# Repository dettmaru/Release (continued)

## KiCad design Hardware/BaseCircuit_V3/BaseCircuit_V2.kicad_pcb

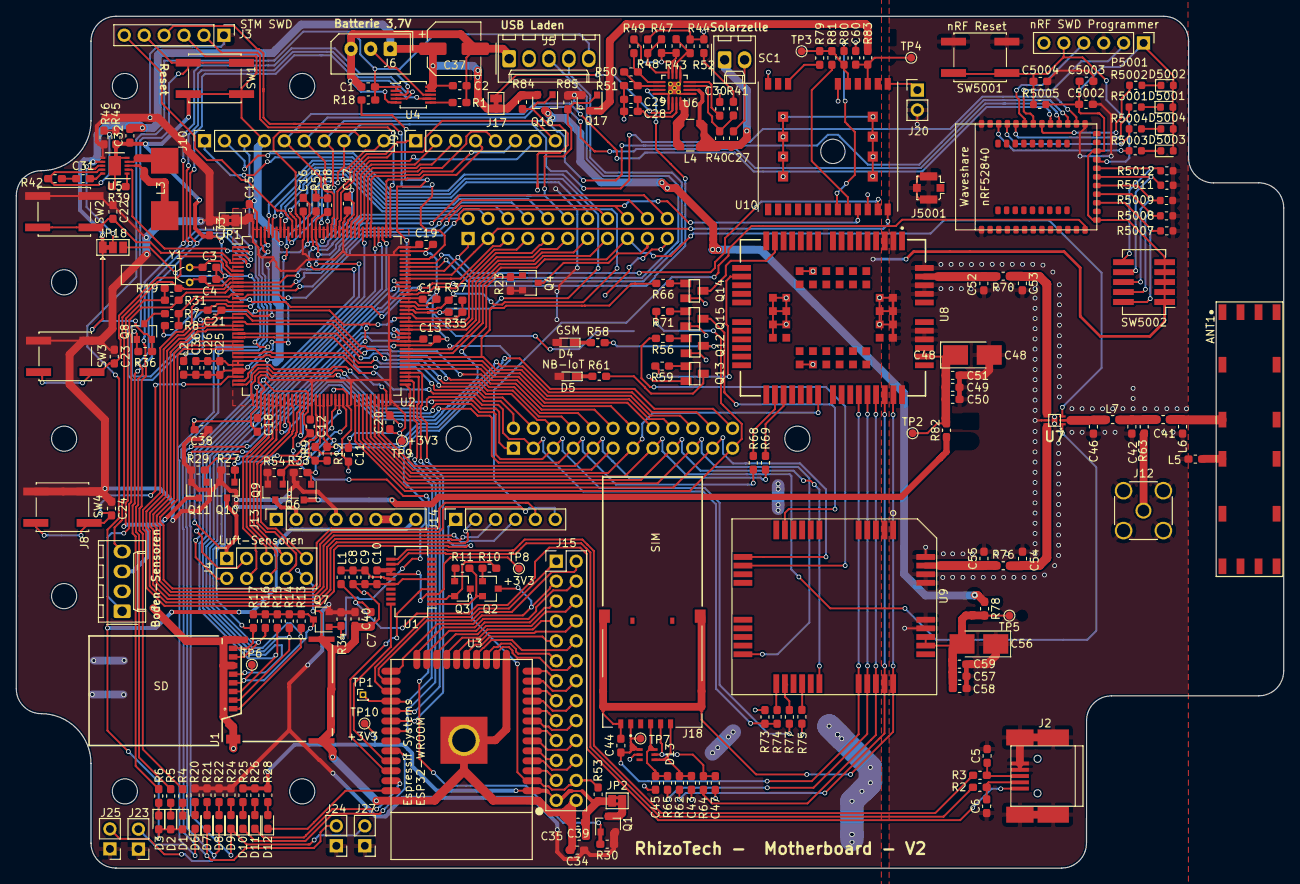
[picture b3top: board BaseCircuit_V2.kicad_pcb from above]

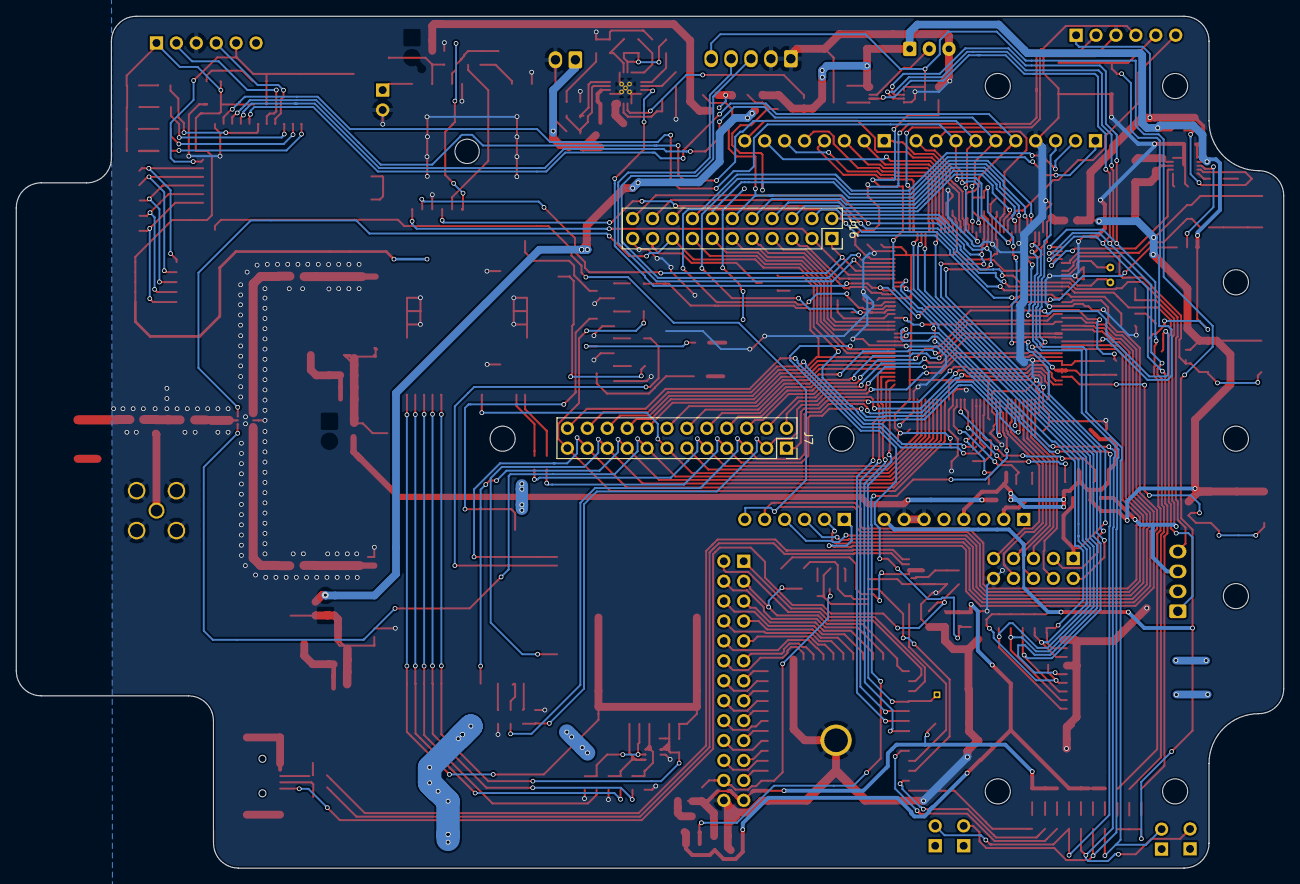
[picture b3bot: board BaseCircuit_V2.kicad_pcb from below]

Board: 2 copper layers, 161.6 x 108.6 mm, 259 parts (2 on the bottom side), 259 nets.

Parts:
ANT1: Lucida; Antenova_Lucida
C1, C2, C25: 1µ; C_0603_1608Metric_Pad1.05x0.95mm_HandSolder
C3, C4: 4p7; C_0603_1608Metric_Pad1.05x0.95mm_HandSolder
C5, C6: 47p; C_0603_1608Metric_Pad1.05x0.95mm_HandSolder
C7, C28, C30, C36: 10n; C_0603_1608Metric_Pad1.05x0.95mm_HandSolder
C8, C10, C11, C12, C13, C14, C15, C16, C17, C18, C19, C20, C21, C22, C23, C24, C26, C31, C35, C44, C49, C57, C60: 100n; C_0603_1608Metric_Pad1.05x0.95mm_HandSolder
C9, C27, C29: 4µ7; C_0603_1608Metric_Pad1.05x0.95mm_HandSolder
C32: 10µ; C_0603_1608Metric_Pad1.05x0.95mm_HandSolder
C33, C34, C38, C39, C40: 22µ; C_0603_1608Metric_Pad1.05x0.95mm_HandSolder
C37: 470µ; CP_Elec_6.3x7.7
C41: 2p2; C_0603_1608Metric_Pad1.05x0.95mm_HandSolder
C42: Not fitted; C_0603_1608Metric_Pad1.05x0.95mm_HandSolder
C43, C45, C47, C59: 33p; C_0603_1608Metric_Pad1.05x0.95mm_HandSolder
C46: 0p5; C_0603_1608Metric_Pad1.05x0.95mm_HandSolder
C48, C56: 100µ; Tantal_Cap_100u
C50: 100p; C_0603_1608Metric_Pad1.05x0.95mm_HandSolder
C51: 22p; C_0603_1608Metric_Pad1.05x0.95mm_HandSolder
C52, C53, C54, C55: NM; C_0603_1608Metric_Pad1.05x0.95mm_HandSolder
C58: 10p; C_0603_1608Metric_Pad1.05x0.95mm_HandSolder
C5002: 4.7µF; C_0603_1608Metric_Pad1.05x0.95mm_HandSolder
C5003, C5004: 100nF; C_0603_1608Metric_Pad1.05x0.95mm_HandSolder
D1, D2, D8, D10: Rot; LED_0603_1608Metric_Pad1.05x0.95mm_HandSolder
D3, D9, D11: Grün; LED_0603_1608Metric_Pad1.05x0.95mm_HandSolder
D4: GSM_NET; GSM_LED
D5: NB-IoT_NET; NB-IoT_LED
D6, D7, D12: Gelb; LED_0603_1608Metric_Pad1.05x0.95mm_HandSolder
D13: SMF05C.TCT; SC70-6
D5001, D5002, D5003, D5004: LED; LED_0603_1608Metric
H6, H7, H8, H9, H10, H11, H12, H13, H14: MountingHole; MountingHole_3.2mm_M3
J1: Micro_SD_Card; 503398-1892
J2: USB B mini; USB_Mini-B
J3: CONN_01X06; PinHeader_1x06_P2.54mm_Vertical
J4: Conn_2x5_Temp; PinHeader_2x05_P2.54mm_Vertical
J5: Conn_01x05; Molex_KK-254_AE-6410-05A_1x05_P2.54mm_Vertical
J6: CONN_01X03; Molex_SPOX_5267-03A_1x03_P2.50mm_Vertical
J7: Conn_02x12_Odd_Even; PinSocket_2x12_P2.54mm_Vertical
J8: Conn_1x4_Soil; Molex_KK-254_AE-6410-04A_1x04_P2.54mm_Vertical
J9, J13: Conn_01x08; PinSocket_1x08_P2.54mm_Vertical
J10: Conn_01x10; PinSocket_1x10_P2.54mm_Vertical
J12: Conn_Coaxial; SMA_Amphenol_132134_Vertical
J14: Conn_01x06; PinSocket_1x06_P2.54mm_Vertical
J15: Conn_02x13_ESP; PinHeader_2x13_P2.54mm_Vertical
J16: Conn_02x11_Odd_Even; PinSocket_2x11_P2.54mm_Vertical
J17: GS2; SolderJumper-2_P1.3mm_Bridged_Pad1.0x1.5mm
J18: Micro-SIM; CONN_78646-3001
J20, J23, J24, J25, J27: Conn_01x02_Male; PinHeader_1x02_P2.54mm_Vertical
J5001: SMA Connector; U.FL_Molex_MCRF_73412-0110_Vertical
JP1: STM Bridge; SolderJumper-2_P1.3mm_Bridged2Bar_Pad1.0x1.5mm
JP2: ESP Bridge; SolderJumper-2_P1.3mm_Bridged2Bar_Pad1.0x1.5mm
JP18: SolderJumper_3_Bridged12; SolderJumper-3_P1.3mm_Bridged12_Pad1.0x1.5mm
L1, L2: Ferrite_Bead; L_0603_1608Metric_Pad1.05x0.95mm_HandSolder
L3: 10µ; MGV0603100M
L4: 22µ; L_Coilcraft_LPS4018
L5, L6: 15n; L_0603_1608Metric_Pad1.05x0.95mm_HandSolder
L7: 3n3; L_0603_1608Metric_Pad1.05x0.95mm_HandSolder
P5001: SWD Programmer; PinHeader_1x06_P2.54mm_Vertical
Q1, Q4, Q6, Q7, Q8, Q9, Q10, Q11, Q16, Q17: DMP2170; SOT-23
Q2, Q3: MMBT2222; SOT-23
Q12, Q13, Q14, Q15: MMBT2222A; SOT23
R1, R4, R5, R6, R7, R8, R18, R19, R20, R21, R22, R24, R25, R26, R28, R31, R58, R61, R68, R69, R74, R77: 1k; R_0603_1608Metric_Pad1.05x0.95mm_HandSolder
R2, R3: 27R; R_0603_1608Metric_Pad1.05x0.95mm_HandSolder
R9, R12, R35, R37, R38, R55, R56, R59, R66, R71: 4k7; R_0603_1608Metric_Pad1.05x0.95mm_HandSolder
R10, R11, R53, R79: 10k; R_0603_1608Metric_Pad1.05x0.95mm_HandSolder
R13, R14, R15, R16, R17: 47k; R_0603_1608Metric_Pad1.05x0.95mm_HandSolder
R23, R27, R29, R30, R33, R34, R36, R54, R84, R85: 1M; R_0603_1608Metric_Pad1.05x0.95mm_HandSolder
R39: 60k4; R_0603_1608Metric_Pad1.05x0.95mm_HandSolder
R40: 3M32; R_0603_1608Metric_Pad1.05x0.95mm_HandSolder
R41: 10M; R_0603_1608Metric_Pad1.05x0.95mm_HandSolder
R42: 15k; R_0603_1608Metric_Pad1.05x0.95mm_HandSolder
R43: 5M49; R_0603_1608Metric_Pad1.05x0.95mm_HandSolder
R44: 4M42; R_0603_1608Metric_Pad1.05x0.95mm_HandSolder
R45: 200k; R_0603_1608Metric_Pad1.05x0.95mm_HandSolder
R46: 340k; R_0603_1608Metric_Pad1.05x0.95mm_HandSolder
R47, R48: 4M99; R_0603_1608Metric_Pad1.05x0.95mm_HandSolder
R49: 1M73; R_0603_1608Metric_Pad1.05x0.95mm_HandSolder
R50: 3M92; R_0603_1608Metric_Pad1.05x0.95mm_HandSolder
R51: 4M32; R_0603_1608Metric_Pad1.05x0.95mm_HandSolder
R52: 6M65; R_0603_1608Metric_Pad1.05x0.95mm_HandSolder
R62, R64, R65: 22R; R_0603_1608Metric_Pad1.05x0.95mm_HandSolder
R63, R70, R75, R76, R78, R82, R83: 0R; R_0603_1608Metric_Pad1.05x0.95mm_HandSolder
R73: 5k6; R_0603_1608Metric_Pad1.05x0.95mm_HandSolder
R80, R81: 2k2; R_0603_1608Metric_Pad1.05x0.95mm_HandSolder
R5001, R5002, R5003, R5004: 220; R_0603_1608Metric
R5005, R5007, R5008, R5009, R5011, R5012: 10k; R_0603_1608Metric
SC1: Solar_Cell; Molex_KK-254_AE-6410-02A_1x02_P2.54mm_Vertical
SW1, SW2, SW3, SW4, SW5001: SW_Push; SW_SPST_EVQQ2
SW5002: SW_DIP_x05; SW_DIP_SPSTx05_Slide_KingTek_DSHP05TJ_W5.25mm_P1.27mm_JPin
TP1: SE_REA; PinHeader_1x01_P1.00mm_Vertical
TP2, TP4, TP8, TP9, TP10: +3V3; TestPoint_Pad_D1.0mm
TP3: +1V8; TestPoint_Pad_D1.0mm
TP5: +VBATT; TestPoint_Pad_D1.0mm
TP6: U_SD; TestPoint_Pad_D1.0mm
TP7: U_SIM; TestPoint_Pad_D1.0mm
U1: FT231XS; SSOP-20_3.9x8.7mm_P0.635mm
U2: STM32L496Zx; TQFP-144_20x20mm_P0.5mm
U3: ESP32-WROOM
U4: MCP73833; MSOP-10_3x3mm_P0.5mm
U5: LTC3440; DFN-10-1EP_3x3mm_P0.5mm_EP1.55x2.48mm
U6: BQ25504; QFN-16-1EP_3x3mm_Pitch0.5mm_ThermalVias_HandSoldering
U7: SKY13370-374LF; SKY13370_374LF
U8: BC95G; BC95-B8
U9: M95; XCVR_M95
U10: A2235-H; XCVR_A2235-H
U5001: nRF52840; Waveshare_nRF528840
Y1: 32.768kHz; Crystal_C26-LF_D2.1mm_L6.5mm_Horizontal

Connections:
1V8: R79.2, R80.2, R81.2, TP3.1, U10.5
+3.3VP: C10.1, TP8.1, U1.3, U1.13, U1.14
+5VL: C1.2, D1.2, D2.2, D3.2, J5.5, J13.8, R18.1, U4.1, U4.2
+5VP: C8.1, C9.1, L1.2, U1.15
+BATT: C2.1, C32.2, C37.1, J6.1, J17.1, JP18.1, Q8.2, Q16.2, R36.1, R84.1, U4.9, U4.10, U5.7
/BT1: C22.2, SW2.2, U2.5
/BT2: C23.2, SW3.2, U2.7
/BT3: C24.2, SW4.2, U2.34
/CLK: J15.8, U3.20
/CMD: J15.9, U3.19
/D_LOAD+: J5.3, U2.104
/D_LOAD-: J5.4, U2.103
/ESP_GPIO0: J15.3, Q2.3, U3.25
/ESP_ON: Q1.1, R30.2, U2.49
/ESP_RESET: J15.24, Q3.3, R53.1, U3.3
/ESP_RXD0: U1.20, U3.34
/ESP_TXD0: U1.4, U3.35
/IO2: J15.4, U3.24
/IO4: J15.2, U3.26
/IO5: U2.75, U3.29
/IO12: J15.13, U3.14
/IO13: J15.12, U3.16
/IO14: J15.14, U3.13
/IO15: J15.5, U3.23
/IO16: J15.1, U3.27
/IO17: TP1.1, U2.73, U3.28
/IO18: U2.76, U3.30
/IO19: U2.74, U3.31
/IO21: D10.1, U3.33
/IO22: D11.1, U3.36
/IO23: D12.1, U3.37
/IO25: J15.17, U3.10
/IO26: J15.16, U3.11
/IO27: J15.15, U3.12
/IO32: J15.19, U3.8
/IO33: J15.18, U3.9
/IO34: J15.21, U3.6
/IO35: J15.20, U3.7
/Interfaces/+5V_ESP: C7.1, J2.1, L1.1
/Interfaces/D+_ESP: C5.1, J2.3, R3.2
/Interfaces/D-_ESP: C6.1, J2.2, R2.2
/Interfaces/DTR: Q2.2, R11.2, U1.1
/Interfaces/RTS: Q3.2, R10.2, U1.2
/LED1: D6.1, J23.2, U2.141
/LED2: D7.1, J24.2, U2.142
/LED3: D8.1, J25.2, U2.85
/LED4: D9.1, J27.2, U2.86
/LOAD_PG: R6.2, U2.3, U4.7
/LOAD_STAT1: R4.2, U2.1, U4.3
/LOAD_STAT2: R5.2, U2.2, U4.4
/MODE_SYNC: U2.4, U5.2
/NRST: J3.5, SW1.1, U2.25
/PA1: J7.1, U2.35
/PA4: J4.4, U2.40
/PA5: J4.5, U2.41
/PA6: J4.6, U2.42
/PA7: J4.7, U2.43
/PA8: J16.5, U2.100
/PA15: J9.4, U2.110
/PB0: J4.8, U2.46
/PB1: J4.9, U2.47
/PB3: J16.6, U2.133
/PB5: J10.10, U2.135
/PB6: J16.8, U2.136
/PB7: J16.10, U2.137
/PB8: J16.12, Q17.1, R85.2, U2.139
/PB9: J16.14, Q16.1, R84.2, U2.140
/PB10: J7.11, U2.69
/PC1: J14.5, U2.27
/PC2: J7.4, U2.28
/PC3: J7.2, U2.29
/PC5: R18.2, U2.45
/PC6: J16.7, U2.96
/PC7: JP18.3, U2.97, U6.11
/PC8: J1.7, R16.2, U2.98
/PC9: J1.8, R17.2, U2.99
/PC10: J1.1, R13.2, U2.111
/PC11: J1.2, R14.2, U2.112
/PC12: J1.5, U2.113
/PD0: J9.6, U2.114
/PD1: J9.5, U2.115
/PD2: J1.3, R15.2, U2.116
/PD3: J9.3, U2.117
/PD4: J9.2, U2.118
/PD5: J9.7, U2.119
/PD6: J9.8, U2.122
/PD7: J9.1, U2.123
/PD8: J7.14, U2.77
/PD9: J7.16, U2.78
/PD10: J7.18, U2.79
/PD13: J16.15, Q7.1, R34.2, U2.82
/PE7: Q10.1, R27.2, U2.58
/PE8: Q11.1, R29.2, U2.59
/PE9: Q9.1, R54.2, U2.60
/PF0: J8.4, J16.22, R19.2, U2.10
/PF1: J8.1, J16.20, R31.2, U2.11
/PF3: R7.2, R8.1, U2.13
/PF4: J16.16, U2.14
/PF5: J14.1, U2.15
/PF6: J7.8, U2.18
/PF7: J14.2, U2.19
/PF8: J7.12, U2.20
/PF9: J14.3, U2.21
/PF10: J14.4, U2.22
/PF12: Q4.1, R23.2, U2.50
/PF13: R9.2, R12.2, U2.53
/PF14: J7.24, R9.1, U2.54
/PF15: J7.22, R12.1, U2.55
/PG0: Q6.1, R33.2, U2.56
/PG2: J16.13, U2.87
/PG3: J16.11, U2.88
/PG4: J16.9, U2.89
/PG5: Q8.1, R36.2, U2.90
/PG6: R35.1, R37.1, U2.91
/PG7: J10.1, R35.2, U2.92
/PG8: J10.2, R37.2, U2.93
/PG13: J4.2, J16.2, R38.2, U2.128
/PG14: J4.3, J16.4, R55.2, U2.129
/PG15: J10.9, U2.132
/PH0: J7.10, U2.23
/PH1: J7.6, U2.24
/Powersupply/THERM: J6.2, U4.8
/SD1: J15.6, U3.22
/SD2: J15.11, U3.17
/SD3: J15.10, U3.18
/SDO: J15.7, U3.21
/SENSOR_VN: J15.22, U3.5
/SENSOR_VP: J15.23, U3.4
/SWCLK: J3.2, U2.109
/SWDIO: J3.4, U2.105
/TRACESWO: J3.6, U2.134
/VREF: C25.2, C26.2, C36.2, J10.3, L2.2, U2.32, U2.33
ANT: C46.1, L7.2, U7.2
ANT_BC95: J16.17, U2.81, U7.3
ANT_M95: J7.15, U2.67, U7.1
BC95_NETLIGHT: R59.2, U8.18
BC95_RST: J7.20, R66.2, U2.80
ESP3V3: C35.1, C39.1, J15.25, JP2.2, R25.1, R26.1, R28.1, R53.2, TP10.1, U3.2
GND: C1.1, C2.2, C3.2, C4.2, C5.2, C6.2, C7.2, C8.2, C9.2, C10.2, C11.2, C12.2, C13.2, C14.2, C15.2, C16.2, C17.2, C18.2, C19.2, C20.2, C21.2, C25.1, C26.1, C27.1, C28.2, C29.2, C30.2, C32.1, C33.2, C34.2, C35.2, C36.1, C37.2, C38.2, C39.2, C40.2, C42.2, C43.2, C45.2, C46.2, C47.2, C48.2, C49.2, C50.2, C51.2, C52.2, C53.2, C54.2, C55.2, C56.1, C57.1, C58.1, C59.1, C60.1, C5002.2, C5003.2, C5004.2, D13.2, J1.6, J1.9, J2.4, J2.5, J2.6, J3.3, J4.10, J5.1, J5.2, J6.3, J8.2, J10.4, J12.2, J13.6, J13.7, J15.26, J16.21, J20.2, J5001.2, L5.1, L6.2, P5001.3, Q12.2, Q13.2, Q14.2, Q15.2, R1.2, R8.2, R39.2, R44.2, R45.1, R48.2, R51.2, R52.1, R73.2, R75.2, R5007.2, R5008.2, R5009.2, R5011.2, R5012.2, SC1.2, SW1.2, SW5001.2, U1.6, U1.16, U2.16, U2.30, U2.31, U2.38, U2.51, U2.61, U2.71, U2.83, U2.94, U2.107, U2.120, U2.130, U2.138, U2.143, U3.1, U3.15, U3.38, U3.39, U4.5, U5.5, U6.1, U6.5, U6.12, U6.13, U6.17, U7.5, U7.7, U8.2, U8.43, U8.47, U8.48, U8.51, U8.52, U8.54, U8.59, U8.60, U8.61, U8.62, U8.63, U8.64, U8.65, U8.66, U8.71, U8.72, U8.73, U8.74, U8.81, U8.82, U8.83, U8.92, U8.93, U8.94, U9.35, U9.36, U9.37, U9.38, U9.40, U10.6, U10.9, U10.20, U10.23, U10.24, U10.25, U10.26, U10.27, U10.28, U10.29, U10.30, U5001.B7
GPS_ON_SW: J16.18, U2.12, U10.19
LED0: R5001.2, U5001.U24
LED1: R5002.2, U5001.W24
LED2: R5003.2, U5001.L24
LED3: R5004.2, U5001.R24
M95_DTR: J7.19, U2.65, U9.20
M95_NETLIGHT: R56.2, U9.13
M95_ON_SW: J7.23, R71.2, U2.63
M95_STATUS: J7.21, U2.64, U9.12
unnamed: ANT1.3, C41.2, L6.1
unnamed: ANT1.4, L5.2
unnamed: C3.1, U2.8, Y1.1
unnamed: C4.1, U2.9, Y1.2
unnamed: C27.2, L4.1, R40.1, SC1.1, U6.2
unnamed: C28.1, C29.1, U6.15
unnamed: C30.1, U6.4
unnamed: C31.1, U5.10
unnamed: C31.2, R42.1
unnamed: C41.1, C42.1, L7.1, R63.2
unnamed: C43.1, D13.4, J18.C3, R62.1
unnamed: C45.1, D13.6, J18.C2, R65.1
unnamed: C47.1, D13.5, J18.C7, R64.1
unnamed: C48.1, C49.1, C50.1, C51.1, R82.1, TP2.1, U8.45, U8.46
unnamed: C52.1, R70.2, U8.53
unnamed: C55.1, R76.1, U9.39
unnamed: C56.2, C57.2, C58.2, C59.2, R78.2, TP5.1, U9.33, U9.34
unnamed: C60.2, R83.2, TP4.1, U10.3
unnamed: D1.1, R4.1
unnamed: D2.1, R5.1
unnamed: D3.1, R6.1
unnamed: D4.1, R58.2
unnamed: D5.1, R61.2
unnamed: D6.2, R20.2
unnamed: D7.2, R21.2
unnamed: D8.2, R22.2
unnamed: D9.2, R24.2
unnamed: D10.2, R25.2
unnamed: D11.2, R26.2
unnamed: D12.2, R28.2
unnamed: D5001.1, R5001.1
unnamed: D5002.1, R5002.1
unnamed: D5003.1, R5003.1
unnamed: D5004.1, R5004.1
unnamed: J1.4, Q7.3, R13.1, R14.1, R15.1, R16.1, R17.1, TP6.1
unnamed: J12.1, R63.1
unnamed: J17.2, U6.14
unnamed: J20.1, U10.1
unnamed: JP2.1, Q1.3
unnamed: JP18.2, U5.8
unnamed: L3.1, U5.4
unnamed: L3.2, U5.3
unnamed: L4.2, U6.16
unnamed: Q2.1, R10.1
unnamed: Q3.1, R11.1
unnamed: Q8.3, R7.1
unnamed: Q12.1, R56.1
unnamed: Q12.3, R58.1
unnamed: Q13.1, R59.1
unnamed: Q13.3, R61.1
unnamed: Q14.1, R66.1
unnamed: Q14.3, U8.15
unnamed: Q15.1, R71.1
unnamed: Q15.3, U9.10
unnamed: R1.1, U4.6
unnamed: R2.1, U1.12
unnamed: R3.1, U1.11
unnamed: R39.1, U5.1
unnamed: R40.2, R41.1, U6.3
unnamed: R41.2, R52.2
unnamed: R42.2, R45.2, R46.1, U5.9
unnamed: R43.1, R47.1, R49.1, U6.7
unnamed: R43.2, R44.1, U6.6
unnamed: R47.2, R48.1, U6.8
unnamed: R49.2, R50.1, U6.9
unnamed: R50.2, R51.1, U6.10
unnamed: R68.1, U8.29
unnamed: R69.1, U8.30
unnamed: R74.1, U9.21
unnamed: R75.1, U9.24
unnamed: R77.2, U9.22
unnamed: R79.1, U10.7
unnamed: R80.1, U10.17
unnamed: R81.1, U10.18
PWR_SW1: J13.2, Q9.3
PWR_SW2: Q6.3, R82.2
PWR_SW3: C22.1, C23.1, C24.1, C33.1, C34.1, C38.1, C40.1, C5002.1, C5003.1, D4.2, D5.2, D5001.2, D5002.2, D5003.2, D5004.2, J3.1, J13.4, J23.1, J24.1, J25.1, J27.1, JP1.2, P5001.1, Q1.2, Q4.2, Q6.2, Q7.2, Q9.2, Q10.2, Q11.2, Q17.2, R20.1, R21.1, R22.1, R23.1, R24.1, R27.1, R29.1, R30.1, R33.1, R34.1, R46.2, R54.1, R85.1, R5005.1, SW2.1, SW3.1, SW4.1, SW5002.1, SW5002.2, SW5002.3, SW5002.4, SW5002.5, U5.6, U5001.AD2, U5001.B1
PWR_SW4: J16.19, Q4.3
PWR_SW5: J4.1, Q10.3, R38.1, R55.1
PWR_SW6: J8.3, Q11.3, R19.1, R31.1
PWR_SW7: Q16.3, R78.1
PWR_SW8: Q17.3, R83.1
RF1: C53.1, R70.1, U7.4
RF2: C54.1, R76.2, U7.6
Reset: C5004.1, P5001.5, R5005.2, SW5001.1, U5001.AC13
SMSPIN_BC95: J7.13, U2.68, U8.34
SMSPIN_M95: J7.17, U2.66, U9.26
SPI_MISO: J10.6, U2.125, U5001.V23
SPI_MOSI: J10.7, U2.126, U5001.AD22
SPI_SCK: J10.5, U2.124, U5001.Y23
SPI_SS: J10.8, U2.127, U5001.AD18
STM3V3: C11.1, C12.1, C13.1, C14.1, C15.1, C16.1, C17.1, C18.1, C19.1, C20.1, C21.1, JP1.1, L2.1, TP9.1, U2.17, U2.39, U2.52, U2.62, U2.72, U2.84, U2.95, U2.106, U2.108, U2.121, U2.131, U2.144
SW0: R5007.1, SW5002.10, U5001.R1
SW1: R5008.1, SW5002.9, U5001.U1
SW2: R5009.1, SW5002.8, U5001.AC19
SW3: R5011.1, SW5002.7, U5001.AC17
SW4: R5012.1, SW5002.6, U5001.AC15
SWDCLK: P5001.2, U5001.AA24
SWDIO: P5001.4, U5001.AC24
UART_BC95_RX: J7.7, R68.2, U2.44
UART_BC95_TX: J7.9, R69.2, U2.70
UART_GPS_RX: J16.3, U2.101, U10.22
UART_GPS_TX: J16.1, U2.102, U10.21
UART_M95_RX: J7.3, R73.1, R74.2, U2.36
UART_M95_TX: J7.5, R77.1, U2.37
USIM_CLK: R62.2, U8.41, U9.30
USIM_DATA: R64.2, U8.40, U9.29
USIM_GND: C44.1, J18.C5, J18.G1, J18.G2, J18.G3, J18.G4, J18.G5, J18.G6, U8.42, U9.31
USIM_RST: R65.2, U8.39, U9.28
USIM_VDD: C44.2, D13.1, J18.C1, TP7.1, U8.38, U9.27
nRF_Interrupt: J14.6, U2.26, U5001.K2

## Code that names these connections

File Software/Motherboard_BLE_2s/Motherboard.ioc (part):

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Mcu.Name=STM32L496Z(E-G)Tx
Mcu.Package=LQFP144
Mcu.UserName=STM32L496ZGTx
PA0.GPIOParameters=GPIO_PuPd,GPIO_Label,GPIO_ModeDefaultEXTI
PA0.GPIO_Label=BT3
PA0.GPIO_ModeDefaultEXTI=GPIO_MODE_IT_RISING
PA0.GPIO_PuPd=GPIO_PULLDOWN
PA0.Signal=SharedStack_PA0
PA0.Stacked=true
PA1.Mode=Full_Duplex_Master
PA1.Signal=SPI1_SCK
PA10.GPIOParameters=GPIO_Label
PA10.GPIO_Label=GPS_RX
PA10.Mode=Asynchronous
PA10.Signal=USART1_RX
PA11.Mode=Device_Only
PA11.Signal=USB_OTG_FS_DM
PA12.Mode=Device_Only
PA12.Signal=USB_OTG_FS_DP
PA13\ (JTMS/SWDIO).Mode=Trace_Asynchronous_SW
PA13\ (JTMS/SWDIO).Signal=SYS_JTMS-SWDIO
PA14\ (JTCK/SWCLK).Mode=Trace_Asynchronous_SW
PA14\ (JTCK/SWCLK).Signal=SYS_JTCK-SWCLK
PA15\ (JTDI).GPIOParameters=GPIO_Label
PA15\ (JTDI).GPIO_Label=SX1272_DIO2
PA15\ (JTDI).Signal=GPIO_Output
PA2.GPIOParameters=GPIO_Label
PA2.GPIO_Label=M95_TX
PA2.Mode=Asynchronous
PA2.Signal=USART2_TX
PA3.GPIOParameters=GPIO_Label
PA3.GPIO_Label=M95_RX
PA3.Mode=Asynchronous
PA3.Signal=USART2_RX
PA6.Mode=Full_Duplex_Master
PA6.Signal=SPI1_MISO
PA7.Mode=Full_Duplex_Master
PA7.Signal=SPI1_MOSI
PA9.GPIOParameters=GPIO_Label
PA9.GPIO_Label=GPS_TX
PA9.Mode=Asynchronous
PA9.Signal=USART1_TX
PB11.GPIOParameters=GPIO_Label
PB11.GPIO_Label=BC95_RX
PB11.Mode=Asynchronous
PB11.Signal=USART3_RX
PB12.GPIOParameters=GPIO_Label
PB12.GPIO_Label=SE_REA
PB12.Signal=GPXTI12
PB13.Mode=Full_Duplex_Master
PB13.Signal=SPI2_SCK
PB14.Mode=Full_Duplex_Master
PB14.Signal=SPI2_MISO
PB15.Mode=Full_Duplex_Master
PB15.Signal=SPI2_MOSI
PB3\ (JTDO/TRACESWO).Mode=Trace_Asynchronous_SW
PB3\ (JTDO/TRACESWO).Signal=SYS_JTDO-SWO
PB8.GPIOParameters=PinState,GPIO_Label
PB8.GPIO_Label=GPS_ON
PB8.PinState=GPIO_PIN_SET
PB8.Signal=GPIO_Output
PB9.GPIOParameters=PinState,GPIO_Label
PB9.GPIO_Label=M95_ON
PB9.PinState=GPIO_PIN_SET
PB9.Signal=GPIO_Output
PC0.GPIOParameters=GPIO_Label
PC0.GPIO_Label=DEBUG_RX
PC0.Mode=Asynchronous
PC0.Signal=LPUART1_RX
PC1.GPIOParameters=GPIO_Label
PC1.GPIO_Label=DEBUG_TX
PC1.Mode=Asynchronous
PC1.Signal=LPUART1_TX
PC12.Mode=SD_1_bit
PC12.Signal=SDMMC1_CK
PC13.GPIOParameters=GPIO_PuPd,GPIO_Label,GPIO_ModeDefaultEXTI
PC13.GPIO_Label=BT2
PC13.GPIO_ModeDefaultEXTI=GPIO_MODE_IT_RISING
PC13.GPIO_PuPd=GPIO_PULLDOWN
PC13.Signal=SharedStack_PC13
PC13.Stacked=true
PC14-OSC32_IN\ (PC14).Mode=LSE-External-Oscillator
PC14-OSC32_IN\ (PC14).Signal=RCC_OSC32_IN
PC15-OSC32_OUT\ (PC15).Mode=LSE-External-Oscillator
PC15-OSC32_OUT\ (PC15).Signal=RCC_OSC32_OUT
PC4.GPIOParameters=GPIO_Label
PC4.GPIO_Label=BC95_TX
PC4.Mode=Asynchronous
PC4.Signal=USART3_TX
PC5.GPIOParameters=GPIO_Label
PC5.GPIO_Label=USB_PWR
PC5.Mode=SYS_WakeUp4
PC5.Signal=SYS_WKUP5
PC7.GPIOParameters=GPIO_Label
PC7.GPIO_Label=VBATT_OK
PC7.Signal=GPIO_Input
PC8.Mode=SD_1_bit
PC8.Signal=SDMMC1_D0
PD0.GPIOParameters=GPIO_Label
PD0.GPIO_Label=SX1272_DIO0
PD0.Signal=GPIO_Output
PD1.GPIOParameters=GPIO_Label
PD1.GPIO_Label=SX1272_DIO1
PD1.Signal=GPIO_Output
PD11.GPIOParameters=GPIO_Label
PD11.GPIO_Label=BC95_RST
PD11.Signal=GPIO_Output
PD12.GPIOParameters=GPIO_Label
PD12.GPIO_Label=ANT_BC95
PD12.Signal=GPIO_Output
PD13.GPIOParameters=PinState,GPIO_Label
PD13.GPIO_Label=SD_PWR
PD13.PinState=GPIO_PIN_SET
PD13.Signal=GPIO_Output
PD14.GPIOParameters=PinState,GPIO_Label
PD14.GPIO_Label=LED3
PD14.PinState=GPIO_PIN_SET
PD14.Signal=GPIO_Output
PD15.GPIOParameters=PinState,GPIO_Label
PD15.GPIO_Label=LED4
PD15.PinState=GPIO_PIN_SET
PD15.Signal=GPIO_Output
PD2.Mode=SD_1_bit
PD2.Signal=SDMMC1_CMD
PD3.GPIOParameters=GPIO_Label
PD3.GPIO_Label=SX1272_DIO3
PD3.Signal=GPIO_Output
PD4.GPIOParameters=GPIO_Label
PD4.GPIO_Label=SDI12_PWR_12V
PD4.Signal=GPIO_Output
PD5.GPIOParameters=GPIO_Label
PD5.GPIO_Label=SDI12_PWR_5V
PD5.Signal=GPIO_Output
PD6.GPIOParameters=GPIO_Label
PD6.GPIO_Label=SDI12_PWR
PD6.Signal=GPIO_Output
PD7.GPIOParameters=GPIO_Label
PD7.GPIO_Label=SDI12DIR
PD7.Signal=GPIO_Output
PE0.GPIOParameters=GPIO_Label
PE0.GPIO_Label=LED1
PE0.Signal=GPIO_Output
PE1.GPIOParameters=GPIO_Speed,PinState,GPIO_Label
PE1.GPIO_Label=LED2
PE1.GPIO_Speed=GPIO_SPEED_FREQ_VERY_HIGH
PE1.PinState=GPIO_PIN_SET
PE1.Signal=GPIO_Output
PE10.GPIOParameters=PinState,GPIO_Label
PE10.GPIO_Label=M95_ON_SW
PE10.PinState=GPIO_PIN_SET
PE10.Signal=GPIO_Output
PE11.GPIOParameters=GPIO_Label
PE11.GPIO_Label=M95_STATUS
PE11.Signal=GPIO_Output
PE12.GPIOParameters=GPIO_Label
PE12.GPIO_Label=M95_DTR
PE12.Signal=GPIO_Output
PE13.GPIOParameters=GPIO_Label
PE13.GPIO_Label=SMSPIN_M95
PE13.Signal=GPIO_Input
PE14.GPIOParameters=GPIO_Label
PE14.GPIO_Label=ANT_M95
PE14.Signal=GPIO_Output
PE15.GPIOParameters=GPIO_Label
PE15.GPIO_Label=SMSPIN_BC95
PE15.Signal=GPIO_Input
PE2.GPIOParameters=GPIO_PuPd,GPIO_Label
PE2.GPIO_Label=LOAD_STAT1
PE2.GPIO_PuPd=GPIO_NOPULL
PE2.Signal=GPIO_Input
PE3.GPIOParameters=GPIO_PuPd,GPIO_Label
PE3.GPIO_Label=LOAD_STAT2
PE3.GPIO_PuPd=GPIO_NOPULL
PE3.Signal=GPIO_Input
PE4.GPIOParameters=GPIO_PuPd,GPIO_Label
PE4.GPIO_Label=LOAD_PG
PE4.GPIO_PuPd=GPIO_NOPULL
PE4.Signal=GPIO_Input
PE5.GPIOParameters=PinState,GPIO_Label
PE5.GPIO_Label=MODE_SYNC
PE5.PinState=GPIO_PIN_SET
PE5.Signal=GPIO_Output
PE6.GPIOParameters=GPIO_PuPd,GPIO_Label,GPIO_ModeDefaultEXTI
PE6.GPIO_Label=BT1
PE6.GPIO_ModeDefaultEXTI=GPIO_MODE_IT_RISING
PE6.GPIO_PuPd=GPIO_PULLDOWN
PE6.Signal=SharedStack_PE6
PE6.Stacked=true
PE7.GPIOParameters=PinState,GPIO_Label
PE7.GPIO_Label=PWR_SW5
PE7.PinState=GPIO_PIN_SET
PE7.Signal=GPIO_Output
PE8.GPIOParameters=PinState,GPIO_Label
PE8.GPIO_Label=PWR_SW6
PE8.PinState=GPIO_PIN_SET
PE8.Signal=GPIO_Output
PE9.GPIOParameters=PinState,GPIO_Label
PE9.GPIO_Label=PWR_SW1
PE9.PinState=GPIO_PIN_SET
PE9.Signal=GPIO_Output
PF0.GPIOParameters=GPIO_PuPdOD
PF0.GPIO_PuPdOD=GPIO_NOPULL
PF0.Mode=I2C
PF0.Signal=I2C2_SDA
PF1.GPIOParameters=GPIO_PuPdOD
PF1.GPIO_PuPdOD=GPIO_NOPULL
PF1.Mode=I2C
PF1.Signal=I2C2_SCL
PF10.Signal=GPIO_Output
PF11.GPIOParameters=PinState,GPIO_Label
PF11.GPIO_Label=ESP_ON
PF11.PinState=GPIO_PIN_SET
PF11.Signal=GPIO_Output
PF12.GPIOParameters=PinState,GPIO_Label
PF12.GPIO_Label=NRF_ON
PF12.PinState=GPIO_PIN_SET
PF12.Signal=GPIO_Output
PF14.Signal=I2C4_SCL
PF15.Signal=I2C4_SDA
PF2.GPIOParameters=PinState,GPIO_Label
PF2.GPIO_Label=GPS_ON_SW
PF2.PinState=GPIO_PIN_SET
PF2.Signal=GPIO_Output
PF3.GPIOParameters=GPIO_Label
PF3.GPIO_Label=VBATT_SENSE
PF3.Mode=IN6-Single-Ended
PF3.Signal=ADC3_IN6
PF4.Mode=IN7-Single-Ended
PF4.Signal=ADC3_IN7
PF5.GPIOParameters=GPIO_Label
PF5.GPIO_Label=SX1272_RESET
PF5.Signal=GPIO_Output
PF7.Signal=GPIO_Output
PF9.Signal=GPIO_Input
PG0.GPIOParameters=PinState,GPIO_Label
PG0.GPIO_Label=BC95_ON
PG0.PinState=GPIO_PIN_SET
PG0.Signal=GPIO_Output
PG1.GPIOParameters=PinState,GPIO_Label
PG1.GPIO_Label=PWR_SW3
PG1.PinState=GPIO_PIN_SET
PG1.Signal=GPIO_Output
PG10.Mode=Full_Duplex_Master
PG10.Signal=SPI3_MISO
PG11.Mode=Full_Duplex_Master
PG11.Signal=SPI3_MOSI
PG12.Signal=GPIO_Output
PG13.Mode=I2C
PG13.Signal=I2C1_SDA
PG14.Mode=I2C
PG14.Signal=I2C1_SCL
PG2.GPIOParameters=PinState,GPIO_Label
PG2.GPIO_Label=NRF_CE
PG2.PinState=GPIO_PIN_SET
PG2.Signal=GPIO_Output
PG3.GPIOParameters=GPIO_PuPd,GPIO_Label
PG3.GPIO_Label=NRF_IRQ
PG3.GPIO_PuPd=GPIO_PULLDOWN
PG3.Signal=SharedStack_PG3
PG3.Stacked=true
PG4.GPIOParameters=PinState,GPIO_Label
PG4.GPIO_Label=NRF_CSN
PG4.PinState=GPIO_PIN_RESET
PG4.Signal=GPIO_Output
PG5.GPIOParameters=GPIO_Speed,PinState,GPIO_Label
PG5.GPIO_Label=SENSE_ON
PG5.GPIO_Speed=GPIO_SPEED_FREQ_LOW
PG5.PinState=GPIO_PIN_SET
PG5.Signal=GPIO_Output
PG8.GPIOParameters=GPIO_Label,GPIO_ModeDefaultEXTI
PG8.GPIO_Label=SDI12_RX
PG8.GPIO_ModeDefaultEXTI=GPIO_MODE_IT_RISING_FALLING
PG8.Signal=GPXTI8
PG9.Mode=Full_Duplex_Master
PG9.Signal=SPI3_SCK
RCC.HSE_VALUE=8000000
RCC.SYSCLKFreq_VALUE=16000000
RCC.SYSCLKSource=RCC_SYSCLKSOURCE_HSI
board=Motherboard

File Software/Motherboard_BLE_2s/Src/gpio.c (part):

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        * EXTI
        * Free pins are configured automatically as Analog (this feature is enabled through
        * the Code Generation settings)
     PF14   ------> I2C4_SCL
     PF15   ------> I2C4_SDA
*/
void MX_GPIO_Init(void)
{
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  HAL_PWREx_EnableVddIO2();

  /*Configure GPIO pin Output Level */
  HAL_GPIO_WritePin(GPIOE, MODE_SYNC_Pin|PWR_SW5_Pin|PWR_SW6_Pin|PWR_SW1_Pin
                          |M95_ON_SW_Pin|LED2_Pin, GPIO_PIN_SET);

  /*Configure GPIO pin Output Level */
  HAL_GPIO_WritePin(GPIOF, GPS_ON_SW_Pin|ESP_ON_Pin|NRF_ON_Pin, GPIO_PIN_SET);

  /*Configure GPIO pin Output Level */
  HAL_GPIO_WritePin(GPIOF, SX1272_RESET_Pin|GPIO_PIN_7|GPIO_PIN_10, GPIO_PIN_RESET);
  HAL_GPIO_WritePin(GPIOF, GPIO_PIN_7, GPIO_PIN_SET);

  /*Configure GPIO pin Output Level */
  HAL_GPIO_WritePin(GPIOG, BC95_ON_Pin|PWR_SW3_Pin|NRF_CE_Pin|SENSE_ON_Pin, GPIO_PIN_SET);

  /*Configure GPIO pin Output Level */
  HAL_GPIO_WritePin(GPIOE, M95_STATUS_Pin|M95_DTR_Pin|ANT_M95_Pin|LED1_Pin, GPIO_PIN_RESET);

  /*Configure GPIO pin Output Level */
  HAL_GPIO_WritePin(GPIOD, BC95_RST_Pin|ANT_BC95_Pin|SX1272_DIO0_Pin|SX1272_DIO1_Pin
                          |SX1272_DIO3_Pin|SDI12_PWR_12V_Pin|SDI12_PWR_5V_Pin|SDI12_PWR_Pin
                          |SDI12DIR_Pin, GPIO_PIN_RESET);

  /*Configure GPIO pin Output Level */
  HAL_GPIO_WritePin(GPIOD, SD_PWR_Pin|LED3_Pin|LED4_Pin, GPIO_PIN_SET);

  /*Configure GPIO pin Output Level */
  HAL_GPIO_WritePin(GPIOG, NRF_CSN_Pin|GPIO_PIN_12, GPIO_PIN_RESET);
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
  /*Configure GPIO pins : PEPin PEPin PEPin PEPin
                           PEPin */
  GPIO_InitStruct.Pin = LOAD_STAT1_Pin|LOAD_STAT2_Pin|LOAD_PG_Pin|SMSPIN_M95_Pin
                          |SMSPIN_BC95_Pin;
  GPIO_InitStruct.Mode = GPIO_MODE_INPUT;
  GPIO_InitStruct.Pull = GPIO_NOPULL;
  HAL_GPIO_Init(GPIOE, &GPIO_InitStruct);
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  /*Configure GPIO pins : PEPin PEPin PEPin PEPin
                           PEPin PEPin PEPin PEPin
                           PEPin */
  GPIO_InitStruct.Pin = MODE_SYNC_Pin|PWR_SW5_Pin|PWR_SW6_Pin|PWR_SW1_Pin
                          |M95_ON_SW_Pin|M95_STATUS_Pin|M95_DTR_Pin|ANT_M95_Pin
                          |LED1_Pin;
  GPIO_InitStruct.Mode = GPIO_MODE_OUTPUT_PP;
  GPIO_InitStruct.Pull = GPIO_NOPULL;
  GPIO_InitStruct.Speed = GPIO_SPEED_FREQ_LOW;
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  GPIO_InitStruct.Pull = GPIO_PULLDOWN;
  HAL_GPIO_Init(BT2_GPIO_Port, &GPIO_InitStruct);

  /*Configure GPIO pins : PFPin PFPin PF7 PF10
                           PFPin PFPin */
  GPIO_InitStruct.Pin = GPS_ON_SW_Pin|SX1272_RESET_Pin|GPIO_PIN_7|GPIO_PIN_10
                          |ESP_ON_Pin|NRF_ON_Pin;
  GPIO_InitStruct.Mode = GPIO_MODE_OUTPUT_PP;
  GPIO_InitStruct.Pull = GPIO_NOPULL;
  GPIO_InitStruct.Speed = GPIO_SPEED_FREQ_LOW;
  HAL_GPIO_Init(GPIOF, &GPIO_InitStruct);

  /*Configure GPIO pins : PF6 PF8 PF13 */
  GPIO_InitStruct.Pin = GPIO_PIN_6|GPIO_PIN_8|GPIO_PIN_13;
  GPIO_InitStruct.Mode = GPIO_MODE_ANALOG;
  GPIO_InitStruct.Pull = GPIO_NOPULL;
  HAL_GPIO_Init(GPIOF, &GPIO_InitStruct);

  /*Configure GPIO pin : PF9 */
  GPIO_InitStruct.Pin = GPIO_PIN_9;
  GPIO_InitStruct.Mode = GPIO_MODE_INPUT;
  GPIO_InitStruct.Pull = GPIO_NOPULL;
  HAL_GPIO_Init(GPIOF, &GPIO_InitStruct);

  /*Configure GPIO pins : PH0 PH1 PH3 */
  GPIO_InitStruct.Pin = GPIO_PIN_0|GPIO_PIN_1|GPIO_PIN_3;
  GPIO_InitStruct.Mode = GPIO_MODE_ANALOG;
  GPIO_InitStruct.Pull = GPIO_NOPULL;
  HAL_GPIO_Init(GPIOH, &GPIO_InitStruct);

  /*Configure GPIO pins : PC2 PC3 PC6 PC9
                           PC10 PC11 */
  GPIO_InitStruct.Pin = GPIO_PIN_2|GPIO_PIN_3|GPIO_PIN_6|GPIO_PIN_9
                          |GPIO_PIN_10|GPIO_PIN_11;
  GPIO_InitStruct.Mode = GPIO_MODE_ANALOG;
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  GPIO_InitStruct.Pull = GPIO_PULLDOWN;
  HAL_GPIO_Init(BT3_GPIO_Port, &GPIO_InitStruct);

  /*Configure GPIO pins : PA4 PA5 PA8 */
  GPIO_InitStruct.Pin = GPIO_PIN_4|GPIO_PIN_5|GPIO_PIN_8;
  GPIO_InitStruct.Mode = GPIO_MODE_ANALOG;
  GPIO_InitStruct.Pull = GPIO_NOPULL;
  HAL_GPIO_Init(GPIOA, &GPIO_InitStruct);

  /*Configure GPIO pins : PB0 PB1 PB2 PB10
                           PB4 PB5 PB6 PB7 */
  GPIO_InitStruct.Pin = GPIO_PIN_0|GPIO_PIN_1|GPIO_PIN_2|GPIO_PIN_10
                          |GPIO_PIN_4|GPIO_PIN_5|GPIO_PIN_6|GPIO_PIN_7;
  GPIO_InitStruct.Mode = GPIO_MODE_ANALOG;
  GPIO_InitStruct.Pull = GPIO_NOPULL;
  HAL_GPIO_Init(GPIOB, &GPIO_InitStruct);

  /*Configure GPIO pins : PF14 PF15 */
  GPIO_InitStruct.Pin = GPIO_PIN_14|GPIO_PIN_15;
  GPIO_InitStruct.Mode = GPIO_MODE_AF_OD;
  GPIO_InitStruct.Pull = GPIO_PULLUP;
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
  /*Configure GPIO pins : PGPin PGPin PGPin PGPin
                           PGPin PG12 */
  GPIO_InitStruct.Pin = BC95_ON_Pin|PWR_SW3_Pin|NRF_CE_Pin|NRF_CSN_Pin
                          |SENSE_ON_Pin|GPIO_PIN_12;
  GPIO_InitStruct.Mode = GPIO_MODE_OUTPUT_PP;
  GPIO_InitStruct.Pull = GPIO_NOPULL;
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  GPIO_InitStruct.Pull = GPIO_NOPULL;
  HAL_GPIO_Init(SE_REA_GPIO_Port, &GPIO_InitStruct);

  /*Configure GPIO pins : PD8 PD9 PD10 */
  GPIO_InitStruct.Pin = GPIO_PIN_8|GPIO_PIN_9|GPIO_PIN_10;
  GPIO_InitStruct.Mode = GPIO_MODE_ANALOG;
  GPIO_InitStruct.Pull = GPIO_NOPULL;
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  /*Configure GPIO pins : PDPin PDPin PDPin PDPin
                           PDPin PDPin PDPin PDPin
                           PDPin PDPin PDPin PDPin */
  GPIO_InitStruct.Pin = BC95_RST_Pin|ANT_BC95_Pin|SD_PWR_Pin|LED3_Pin
                          |LED4_Pin|SX1272_DIO0_Pin|SX1272_DIO1_Pin|SX1272_DIO3_Pin
                          |SDI12_PWR_12V_Pin|SDI12_PWR_5V_Pin|SDI12_PWR_Pin|SDI12DIR_Pin;
  GPIO_InitStruct.Mode = GPIO_MODE_OUTPUT_PP;
  GPIO_InitStruct.Pull = GPIO_NOPULL;
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  GPIO_InitStruct.Pull = GPIO_PULLDOWN;
  HAL_GPIO_Init(NRF_IRQ_GPIO_Port, &GPIO_InitStruct);

  /*Configure GPIO pins : PG6 PG7 PG15 */
  GPIO_InitStruct.Pin = GPIO_PIN_6|GPIO_PIN_7|GPIO_PIN_15;
  GPIO_InitStruct.Mode = GPIO_MODE_ANALOG;
  GPIO_InitStruct.Pull = GPIO_NOPULL;
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  HAL_GPIO_Init(GPIOB, &GPIO_InitStruct);

  /*Configure GPIO pin : PtPin */
  GPIO_InitStruct.Pin = LED2_Pin;
  GPIO_InitStruct.Mode = GPIO_MODE_OUTPUT_PP;
  GPIO_InitStruct.Pull = GPIO_NOPULL;
  GPIO_InitStruct.Speed = GPIO_SPEED_FREQ_VERY_HIGH;
  HAL_GPIO_Init(LED2_GPIO_Port, &GPIO_InitStruct);

  /* EXTI interrupt init*/
  HAL_NVIC_SetPriority(EXTI0_IRQn, 0, 0);
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
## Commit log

2022-01-10 Release
